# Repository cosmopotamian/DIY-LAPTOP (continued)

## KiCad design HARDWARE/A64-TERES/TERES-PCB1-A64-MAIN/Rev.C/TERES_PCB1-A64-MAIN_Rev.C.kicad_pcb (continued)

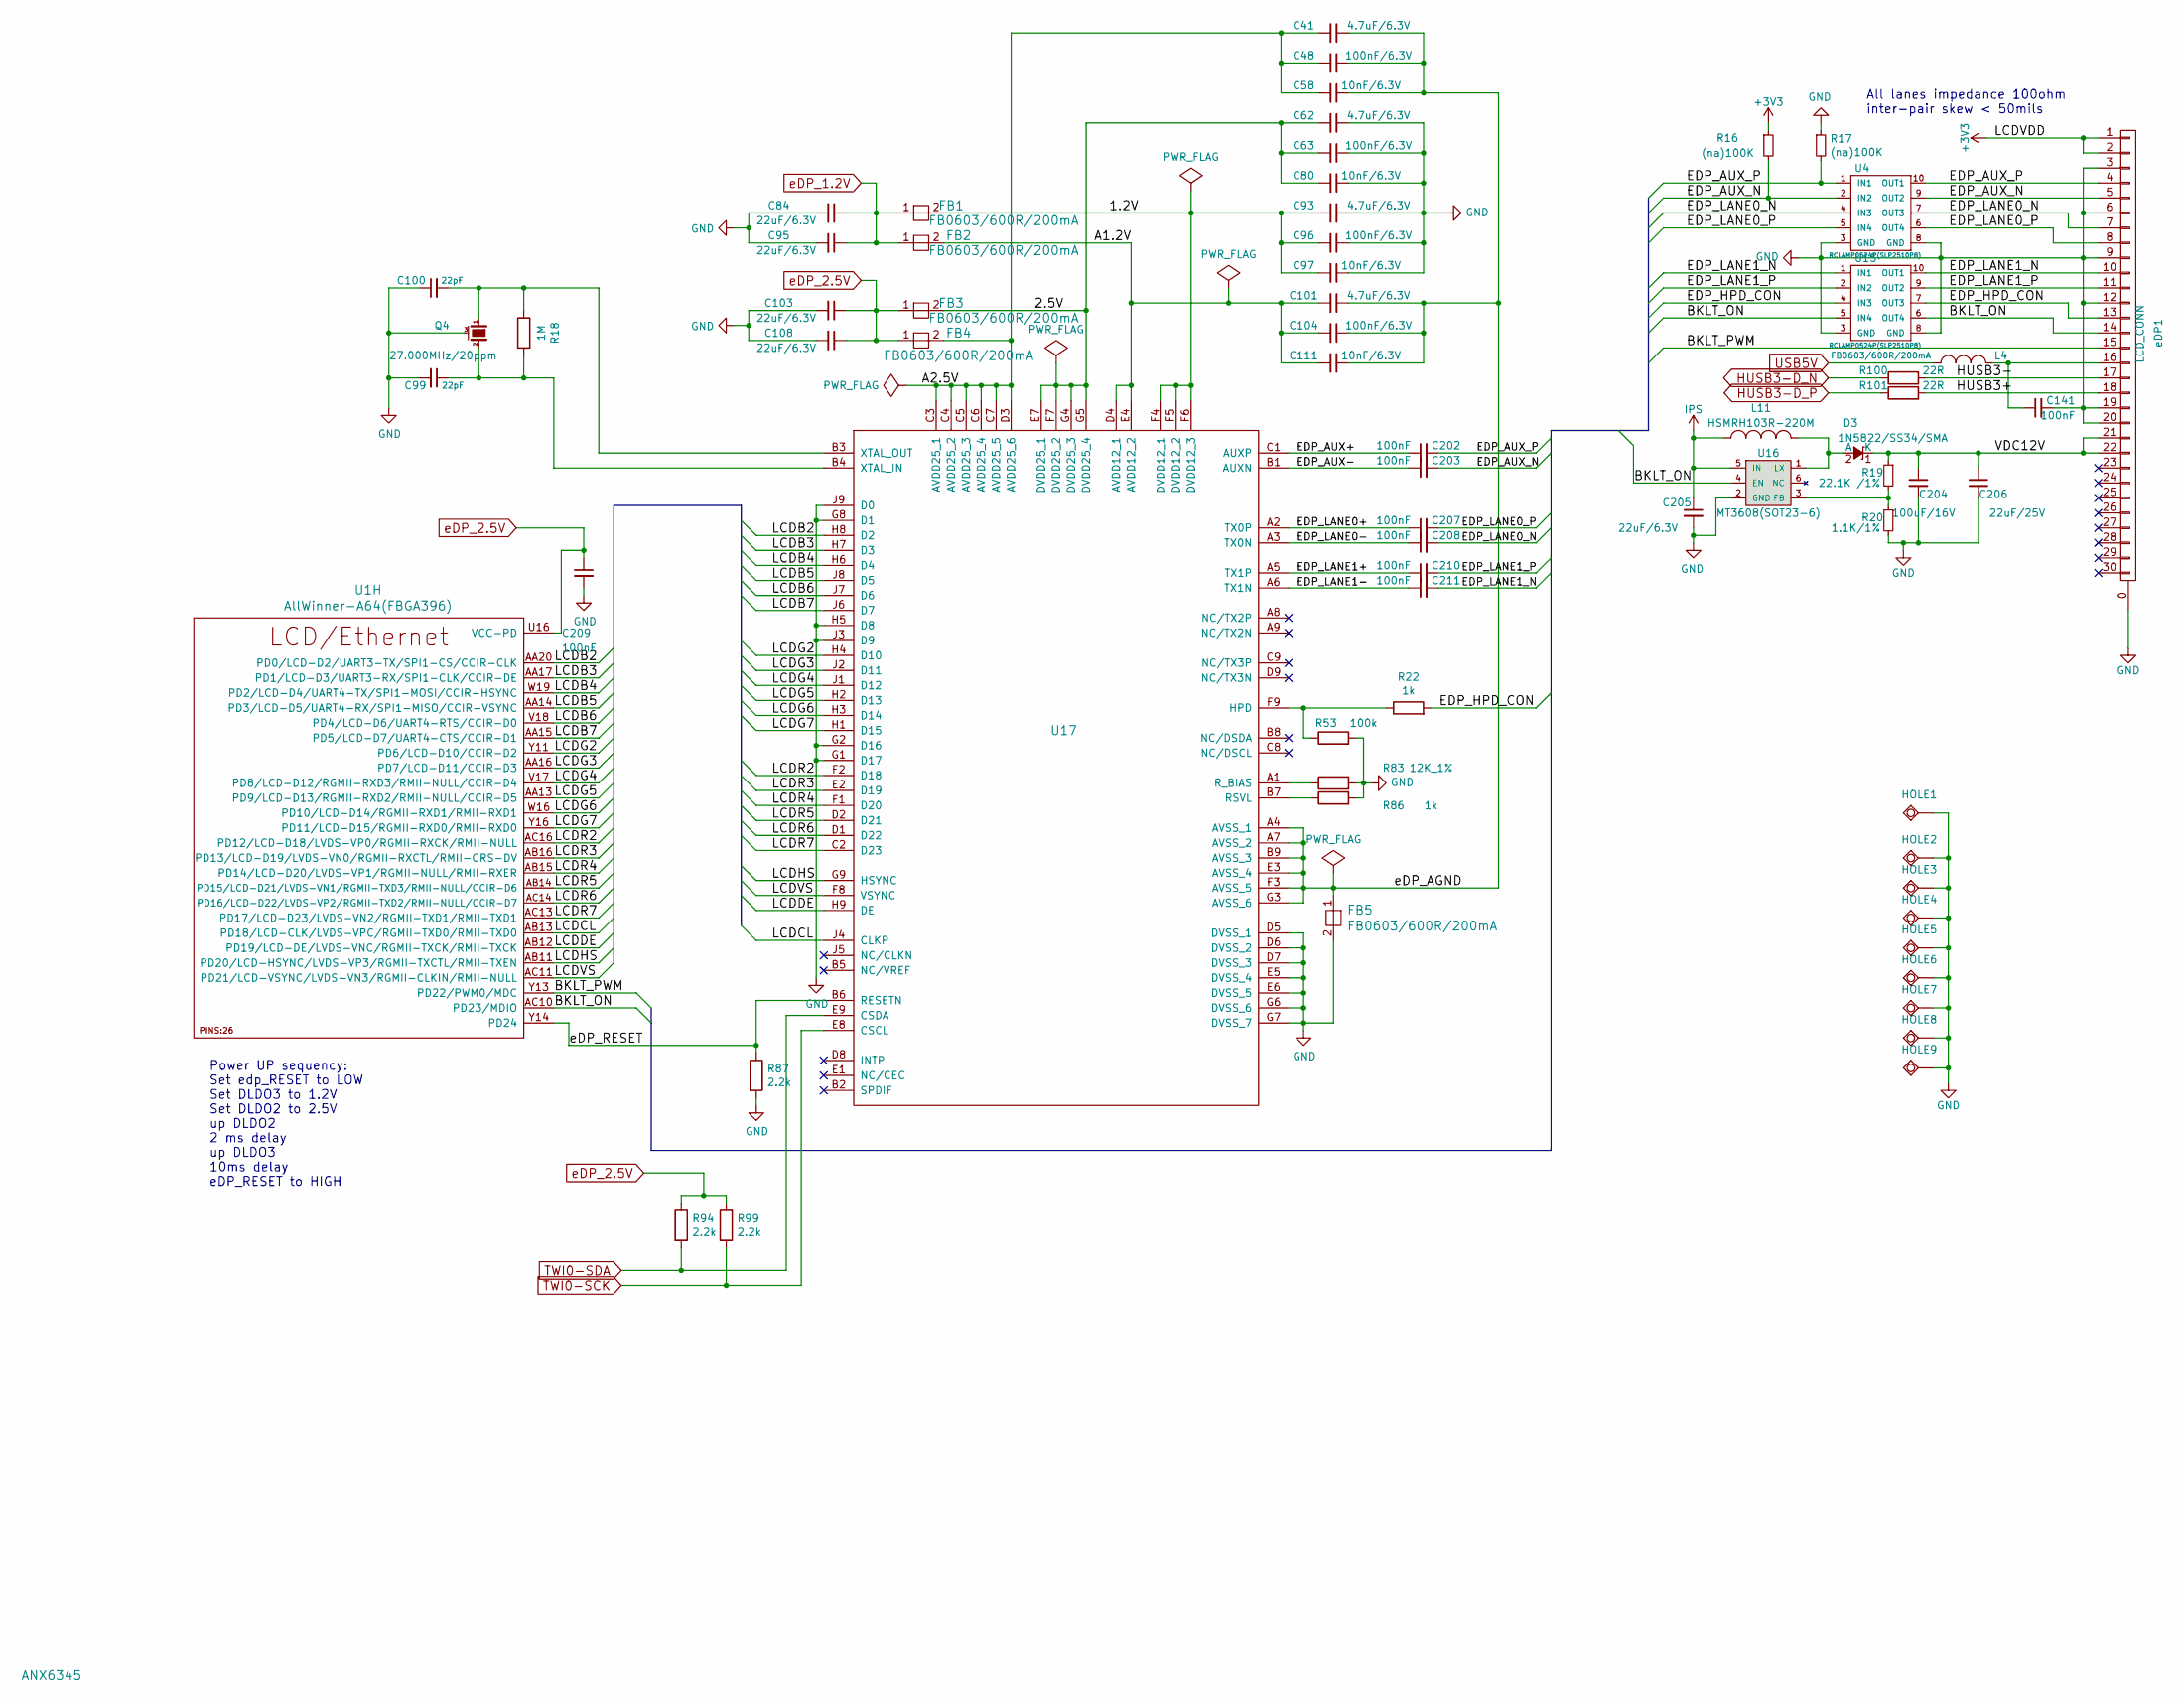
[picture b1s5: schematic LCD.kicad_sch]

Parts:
C41, C62, C93, C101: 4.7uF/6.3V; C_0603_5MIL_DWS
C48, C63, C96, C104: 100nF/6.3V; C_0402_5MIL_DWS
C58, C80, C97, C111: 10nF/6.3V; C_0402_5MIL_DWS
C84, C95, C103, C108, C205: 22uF/6.3V; C_0603_5MIL_DWS
C99, C100: 22pF; C_0402_5MIL_DWS
C141, C202, C203, C207, C208, C209, C210, C211: 100nF; C_0402_5MIL_DWS
C204: 100uF/16V; C_1206_5MIL_DWS
C206: 22uF/25V; C_1206_5MIL_DWS
D3: 1N5822/SS34/SMA; SMA-KA
FB1, FB2, FB3, FB4, FB5: FB0603/600R/200mA; L_0603_5MIL_DWS
HOLE1, HOLE2, HOLE3, HOLE4, HOLE5, HOLE6, HOLE7, HOLE8, HOLE9: TESTPAD; Oval_Drill
L4: FB0603/600R/200mA; L_0603_5MIL_DWS
L11: HSMRH103R-220M; HSMRH103R
Q4: 27.000MHz/20ppm; TSX-3.2x2.5mm_GND(3)
R16, R17: (na)100K; R_0402_5MIL_DWS
R18: 1M; R_0402_5MIL_DWS
R19: 22.1K /1%; R_0402_5MIL_DWS
R20: 1.1K/1%; R_0402_5MIL_DWS
R22, R86: 1k; R_0402_5MIL_DWS
R53: 100k; R_0402_5MIL_DWS
R83: 12K_1%; R_0402_5MIL_DWS
R87, R94, R99: 2.2k; R_0402_5MIL_DWS
R100, R101: 22R; R_0402_5MIL_DWS
U1: AllWinner-A64(FBGA396); FBGA396
U4, U15: RCLAMP0524P(SLP2510P8); SLP2510P8
U16: MT3608(SOT23-6); SOT23-6
U17: ANX6345; BGA_8x8mm_81p_0.8
eDP1: LCD_CONN; eDP-TERES

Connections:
+3V3: R16.1, eDP1.1, eDP1.2; also elsewhere on the board
/eDP LCD/1.2V: C93.2, C96.2, C97.2, FB1.2, U17.F4 (DVDD12_1), U17.F5 (DVDD12_2), U17.F6 (DVDD12_3)
/eDP LCD/2.5V: C62.2, C63.2, C80.2, FB3.2, U17.E7 (DVDD25_1), U17.F7 (DVDD25_2), U17.G4 (DVDD25_3), U17.G5 (DVDD25_4)
/eDP LCD/A1.2V: C101.2, C104.2, C111.2, FB2.2, U17.D4 (AVDD12_1), U17.E4 (AVDD12_2)
/eDP LCD/A2.5V: C41.2, C48.2, C58.2, FB4.2, U17.C3 (AVDD25_1), U17.C4 (AVDD25_2), U17.C5 (AVDD25_3), U17.C6 (AVDD25_4), U17.C7 (AVDD25_5), U17.D3 (AVDD25_6)
/eDP LCD/BKLT_ON: U1.AC10 (PD23/MDIO), U15.5 (IN4), U15.6 (OUT4), U16.4 (EN), eDP1.14
/eDP LCD/BKLT_PWM: U1.Y13 (PD22/PWM0/MDC), eDP1.15
/eDP LCD/EDP_AUX+: C202.1, U17.C1 (AUXP)
/eDP LCD/EDP_AUX-: C203.1, U17.B1 (AUXN)
/eDP LCD/EDP_AUX_N: C203.2, R16.2, U4.2 (IN2), U4.9 (OUT2), eDP1.5
/eDP LCD/EDP_AUX_P: C202.2, R17.2, U4.1 (IN1), U4.10 (OUT1), eDP1.4
/eDP LCD/EDP_HPD_CON: R22.2, U15.4 (IN3), U15.7 (OUT3), eDP1.13
/eDP LCD/EDP_LANE0+: C207.1, U17.A2 (TX0P)
/eDP LCD/EDP_LANE0-: C208.1, U17.A3 (TX0N)
/eDP LCD/EDP_LANE0_N: C208.2, U4.4 (IN3), U4.7 (OUT3), eDP1.7
/eDP LCD/EDP_LANE0_P: C207.2, U4.5 (IN4), U4.6 (OUT4), eDP1.8
/eDP LCD/EDP_LANE1+: C210.1, U17.A5 (TX1P)
/eDP LCD/EDP_LANE1-: C211.1, U17.A6 (TX1N)
/eDP LCD/EDP_LANE1_N: C211.2, U15.1 (IN1), U15.10 (OUT1), eDP1.10
/eDP LCD/EDP_LANE1_P: C210.2, U15.2 (IN2), U15.9 (OUT2), eDP1.11
/eDP LCD/HUSB3+: R101.2, eDP1.18
/eDP LCD/HUSB3-: R100.2, eDP1.17
/eDP LCD/LCDB2: U1.AA20 (PD0/LCD-D2/UART3-TX/SPI1-CS/CCIR-CLK), U17.H8 (D2)
/eDP LCD/LCDB3: U1.AA17 (PD1/LCD-D3/UART3-RX/SPI1-CLK/CCIR-DE), U17.H7 (D3)
/eDP LCD/LCDB4: U1.W19 (PD2/LCD-D4/UART4-TX/SPI1-MOSI/CCIR-HSYNC), U17.H6 (D4)
/eDP LCD/LCDB5: U1.AA14 (PD3/LCD-D5/UART4-RX/SPI1-MISO/CCIR-VSYNC), U17.J8 (D5)
/eDP LCD/LCDB6: U1.V18 (PD4/LCD-D6/UART4-RTS/CCIR-D0), U17.J7 (D6)
/eDP LCD/LCDB7: U1.AA15 (PD5/LCD-D7/UART4-CTS/CCIR-D1), U17.J6 (D7)
/eDP LCD/LCDCL: U1.AB13 (PD18/LCD-CLK/LVDS-VPC/RGMII-TXD0/RMII-T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), U17.J4 (CLKP)
/eDP LCD/LCDDE: U1.AB12 (PD19/LCD-DE/LVDS-VNC/RGMII-TXCK/RMII-TX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), U17.H9 (DE)
/eDP LCD/LCDG2: U1.Y11 (PD6/LCD-D10/CCIR-D2), U17.H4 (D10)
/eDP LCD/LCDG3: U1.AA16 (PD7/LCD-D11/CCIR-D3), U17.J2 (D11)
/eDP LCD/LCDG4: U1.V17 (PD8/LCD-D12/RGMII-RXD3/RMII-NULL/CCIR-D4), U17.J1 (D12)
/eDP LCD/LCDG5: U1.AA13 (PD9/LCD-D13/RGMII-RXD2/RMII-NULL/CCIR-D5), U17.H2 (D13)
/eDP LCD/LCDG6: U1.W16 (PD10/LCD-D14/RGMII-RXD1/RMII-RXD1), U17.H3 (D14)
/eDP LCD/LCDG7: U1.Y16 (PD11/LCD-D15/RGMII-RXD0/RMII-RXD0), U17.H1 (D15)
/eDP LCD/LCDHS: U1.AB11 (PD20/LCD-HSYNC/LVDS-VP3/RGMII-TXCTL/RMI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), U17.G9 (HSYNC)
/eDP LCD/LCDR2: U1.AC16 (PD12/LCD-D18/LVDS-VP0/RGMII-RXCK/RMII-N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), U17.F2 (D18)
/eDP LCD/LCDR3: U1.AB16 (PD13/LCD-D19/LVDS-VN0/RGMII-RXCTL/RMII-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), U17.E2 (D19)
/eDP LCD/LCDR4: U1.AB15 (PD14/LCD-D20/LVDS-VP1/RGMII-NULL/RMII-R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), U17.F1 (D20)
/eDP LCD/LCDR5: U1.AB14 (PD15/LCD-D21/LVDS-VN1/RGMII-TXD3/RMII-N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), U17.D2 (D21)
/eDP LCD/LCDR6: U1.AC14 (PD16/LCD-D22/LVDS-VP2/RGMII-TXD2/RMII-N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), U17.D1 (D22)
/eDP LCD/LCDR7: U1.AC13 (PD17/LCD-D23/LVDS-VN2/RGMII-TXD1/RMII-T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), U17.C2 (D23)
/eDP LCD/LCDVS: U1.AC11 (PD21/LCD-VSYNC/LVDS-VN3/RGMII-CLKIN/RMI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), U17.F8 (VSYNC)
/eDP LCD/VDC18V: C204.1, C206.1, D3.1 (K), R19.1, eDP1.21, eDP1.22
/eDP LCD/eDP_AGND: C41.1, C48.1, C58.1, C101.1, C104.1, C111.1, FB5.1, U17.A4 (AVSS_1), U17.A7 (AVSS_2), U17.B9 (AVSS_3), U17.E3 (AVSS_4), U17.F3 (AVSS_5), U17.G3 (AVSS_6)
/eDP LCD/eDP_RESET: R87.1, U1.Y14 (PD24), U17.B6 (RESETN)
GND: C62.1, C63.1, C80.1, C84.2, C93.1, C95.2, C96.1, C97.1, C99.2, C100.1, C103.2, C108.2, C141.2, C204.2, C205.2, C206.2, C209.2, FB5.2, HOLE1.1, HOLE2.1, HOLE3.1, HOLE4.1, HOLE5.1, HOLE6.1, HOLE7.1, HOLE8.1, HOLE9.1, Q4.3 (case), R17.1, R20.2, R53.2, R83.2, R86.2, R87.2, U4.3 (GND), U4.8 (GND), U15.3 (GND), U15.8 (GND), U16.2 (GND), U17.D5 (DVSS_1), U17.D6 (DVSS_2), U17.D7 (DVSS_3), U17.E5 (DVSS_4), U17.E6 (DVSS_5), U17.G1 (D17), U17.G2 (D16), U17.G6 (DVSS_6), U17.G7 (DVSS_7), U17.G8 (D1), U17.H5 (D8), U17.J3 (D9), U17.J9 (D0), eDP1.0, eDP1.3, eDP1.6, eDP1.9, eDP1.12, eDP1.19, eDP1.20; also elsewhere on the board
HUSB3-D_N: R100.1; also elsewhere on the board
HUSB3-D_P: R101.1; also elsewhere on the board
IPS: C205.1, L11.1, U16.5 (IN); also elsewhere on the board
unnamed: C99.1, Q4.2, R18.2, U17.B4 (XTAL_IN)
unnamed: C100.2, Q4.1, R18.1, U17.B3 (XTAL_OUT)
unnamed: C141.1, L4.1, eDP1.16
unnamed: D3.2 (A), L11.2, U16.1 (LX)
unnamed: R19.2, R20.1, U16.3 (FB)
unnamed: R22.1, R53.1, U17.F9 (HPD)
unnamed: R83.1, U17.A1 (R_BIAS)
unnamed: R86.1, U17.B7 (RSVL)
TWI0-SCK: R99.2, U17.E8 (CSCL); also elsewhere on the board
TWI0-SDA: R94.2, U17.E9 (CSDA); also elsewhere on the board
USB5V: L4.2; also elsewhere on the board
eDP_1.2V: C84.1, C95.1, FB1.1, FB2.1; also elsewhere on the board
eDP_2.5V: C103.1, C108.1, C209.1, FB3.1, FB4.1, R94.1, R99.1, U1.U16 (VCC-PD); also elsewhere on the board

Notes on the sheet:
Power UP sequency: Set edp_RESET to LOW Set DLDO3 to 1.2V Set DLDO2 to 2.5V up DLDO2 2 ms delay up DLDO3 10ms delay eDP_RESET to HIGH
All lanes impedance 100ohm inter-pair skew < 50mils

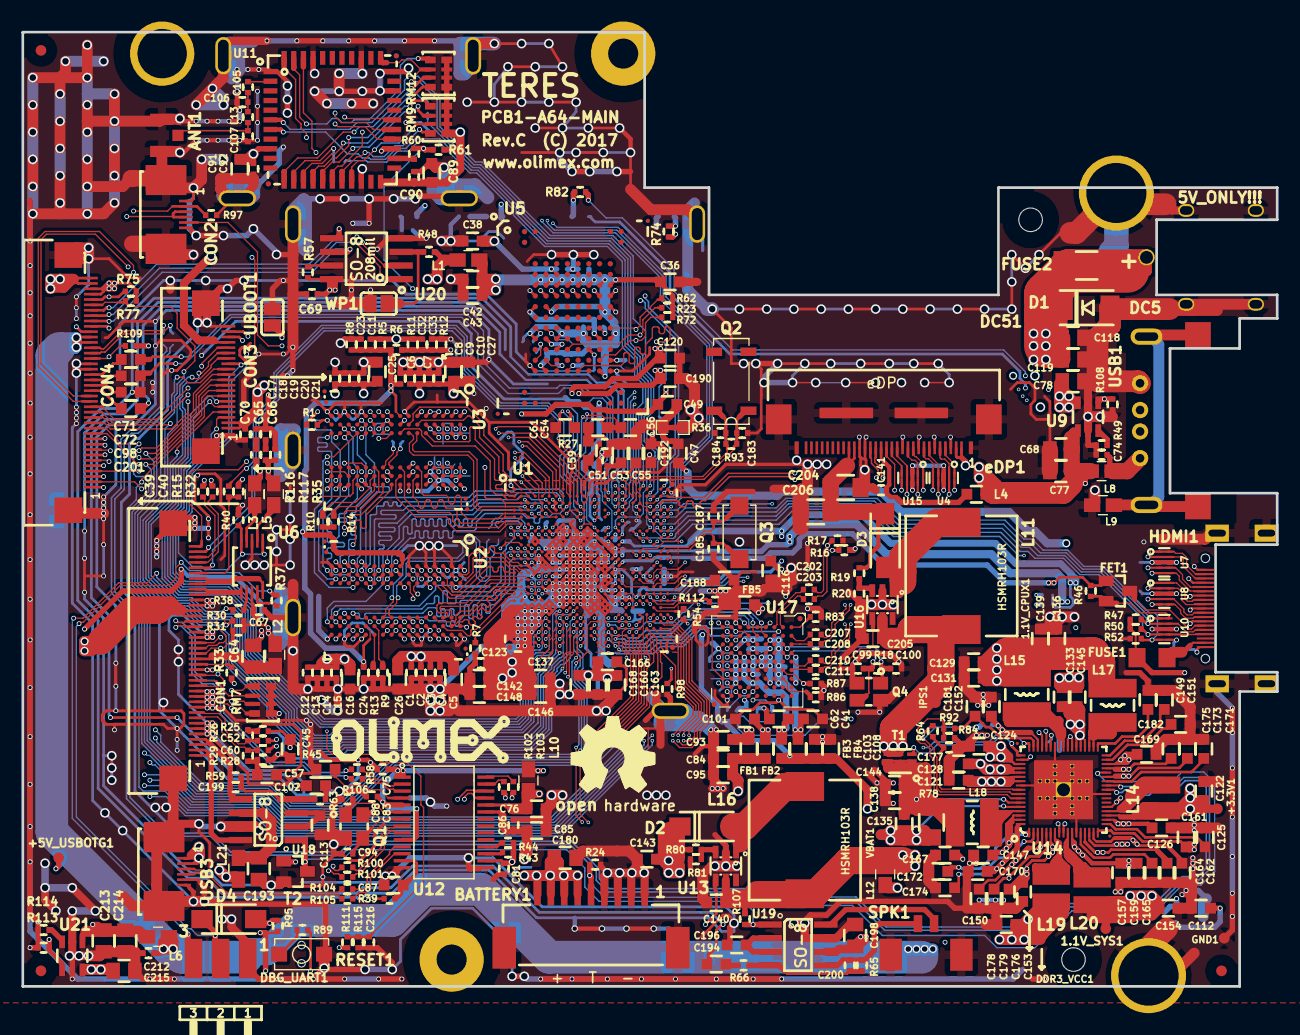
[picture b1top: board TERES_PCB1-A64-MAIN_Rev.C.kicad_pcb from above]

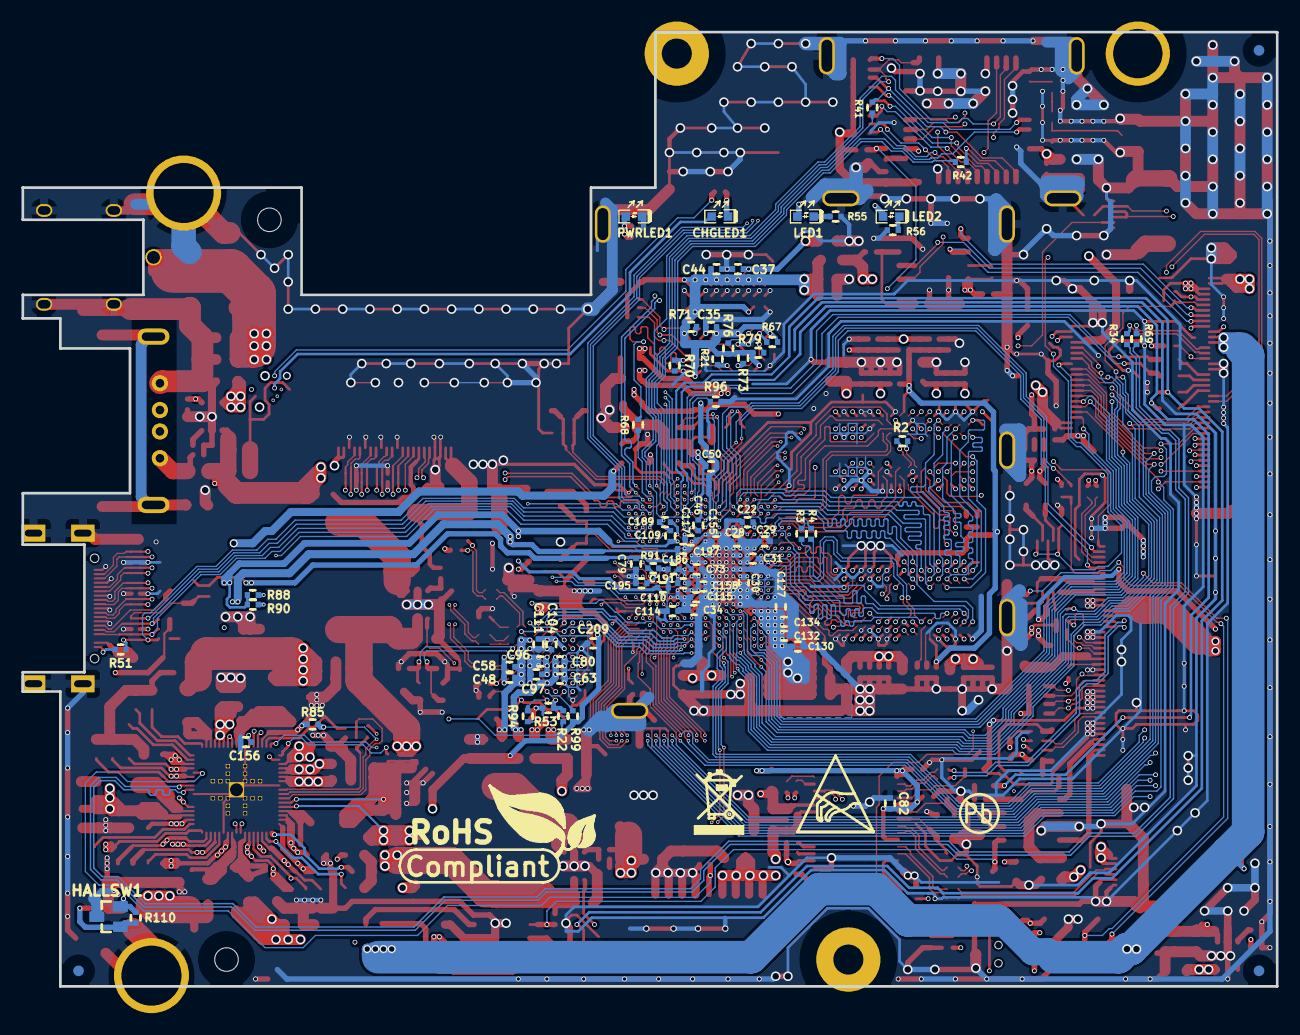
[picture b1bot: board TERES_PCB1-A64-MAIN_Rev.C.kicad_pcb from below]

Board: 6 copper layers, 117.0 x 89.0 mm, 443 parts (75 on the bottom side), 414 nets.

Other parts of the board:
MountingHole: Mounting_hole_3.3mm; Mounting_hole_5.6mm_TERES
MountingHole#2: Mounting_hole_3.3mm; Mounting_hole_5.6mm_TERES
MountingHole#3: Mounting_hole_3.3mm
MountingHole#4: Mounting_hole_3.3mm; Mounting_hole_2.8mm
MountingHole#5: Mounting_hole_3.3mm; Mounting_hole_TERES_4.6mm
MountingHole#6, MountingHole#7: Mounting_hole_3.3mm; NPTH_2.2mm
RM7, RM9, RM12: RA1206_(4x0603)_4B8_100k; R_MATRIX_4
Ref**: Val**; LOGO_ANTISTATIC_1
Ref**#2: Val**; LOGO_ROHS_1

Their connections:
+3V3: RM7.1.1, RM7.2.1, RM7.3.1, RM7.4.1; also elsewhere on the board
/NAND Flash , eMMC, T-Card and Audio/SDC0-D0: RM7.3.2; also elsewhere on the board
/NAND Flash , eMMC, T-Card and Audio/SDC0-D1: RM7.2.2; also elsewhere on the board
/NAND Flash , eMMC, T-Card and Audio/SDC0-D2: RM7.4.2; also elsewhere on the board
/NAND Flash , eMMC, T-Card and Audio/SDC0-DET#: RM7.1.2; also elsewhere on the board
/USB&HDMI,WiFi&BT,Ethernet,LCD/BT-RST-N: RM12.3.2; also elsewhere on the board
/USB&HDMI,WiFi&BT,Ethernet,LCD/BT-UART-RX: RM12.4.2; also elsewhere on the board
/USB&HDMI,WiFi&BT,Ethernet,LCD/WL-PMU-EN: RM12.2.2; also elsewhere on the board
/USB&HDMI,WiFi&BT,Ethernet,LCD/WL-SDIO-CMD: RM9.3.2; also elsewhere on the board
/USB&HDMI,WiFi&BT,Ethernet,LCD/WL-SDIO-D0: RM9.1.2; also elsewhere on the board
/USB&HDMI,WiFi&BT,Ethernet,LCD/WL-SDIO-D1: RM9.2.2; also elsewhere on the board
/USB&HDMI,WiFi&BT,Ethernet,LCD/WL-SDIO-D2: RM9.4.2; also elsewhere on the board
/USB&HDMI,WiFi&BT,Ethernet,LCD/WL-SDIO-D3: RM12.1.2; also elsewhere on the board
VCC-PL: RM9.1.1, RM9.2.1, RM9.3.1, RM9.4.1, RM12.1.1, RM12.2.1, RM12.3.1, RM12.4.1; also elsewhere on the board

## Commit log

2025-03-08 Saved with Kicad 9.0
